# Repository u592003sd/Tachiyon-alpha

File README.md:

# Tachiyon-α MCU Developement Board

## Overview
- A minimalist Development Board design for a MSPM0C110x & MSPM0L130x MCUs.
- Low cost ARM Cortex M0+ MCU support

## Features
- Supports USB & SWD connection
- Powers up from Host USB port.

## Software Resources
- To be updated post PCB bring up.

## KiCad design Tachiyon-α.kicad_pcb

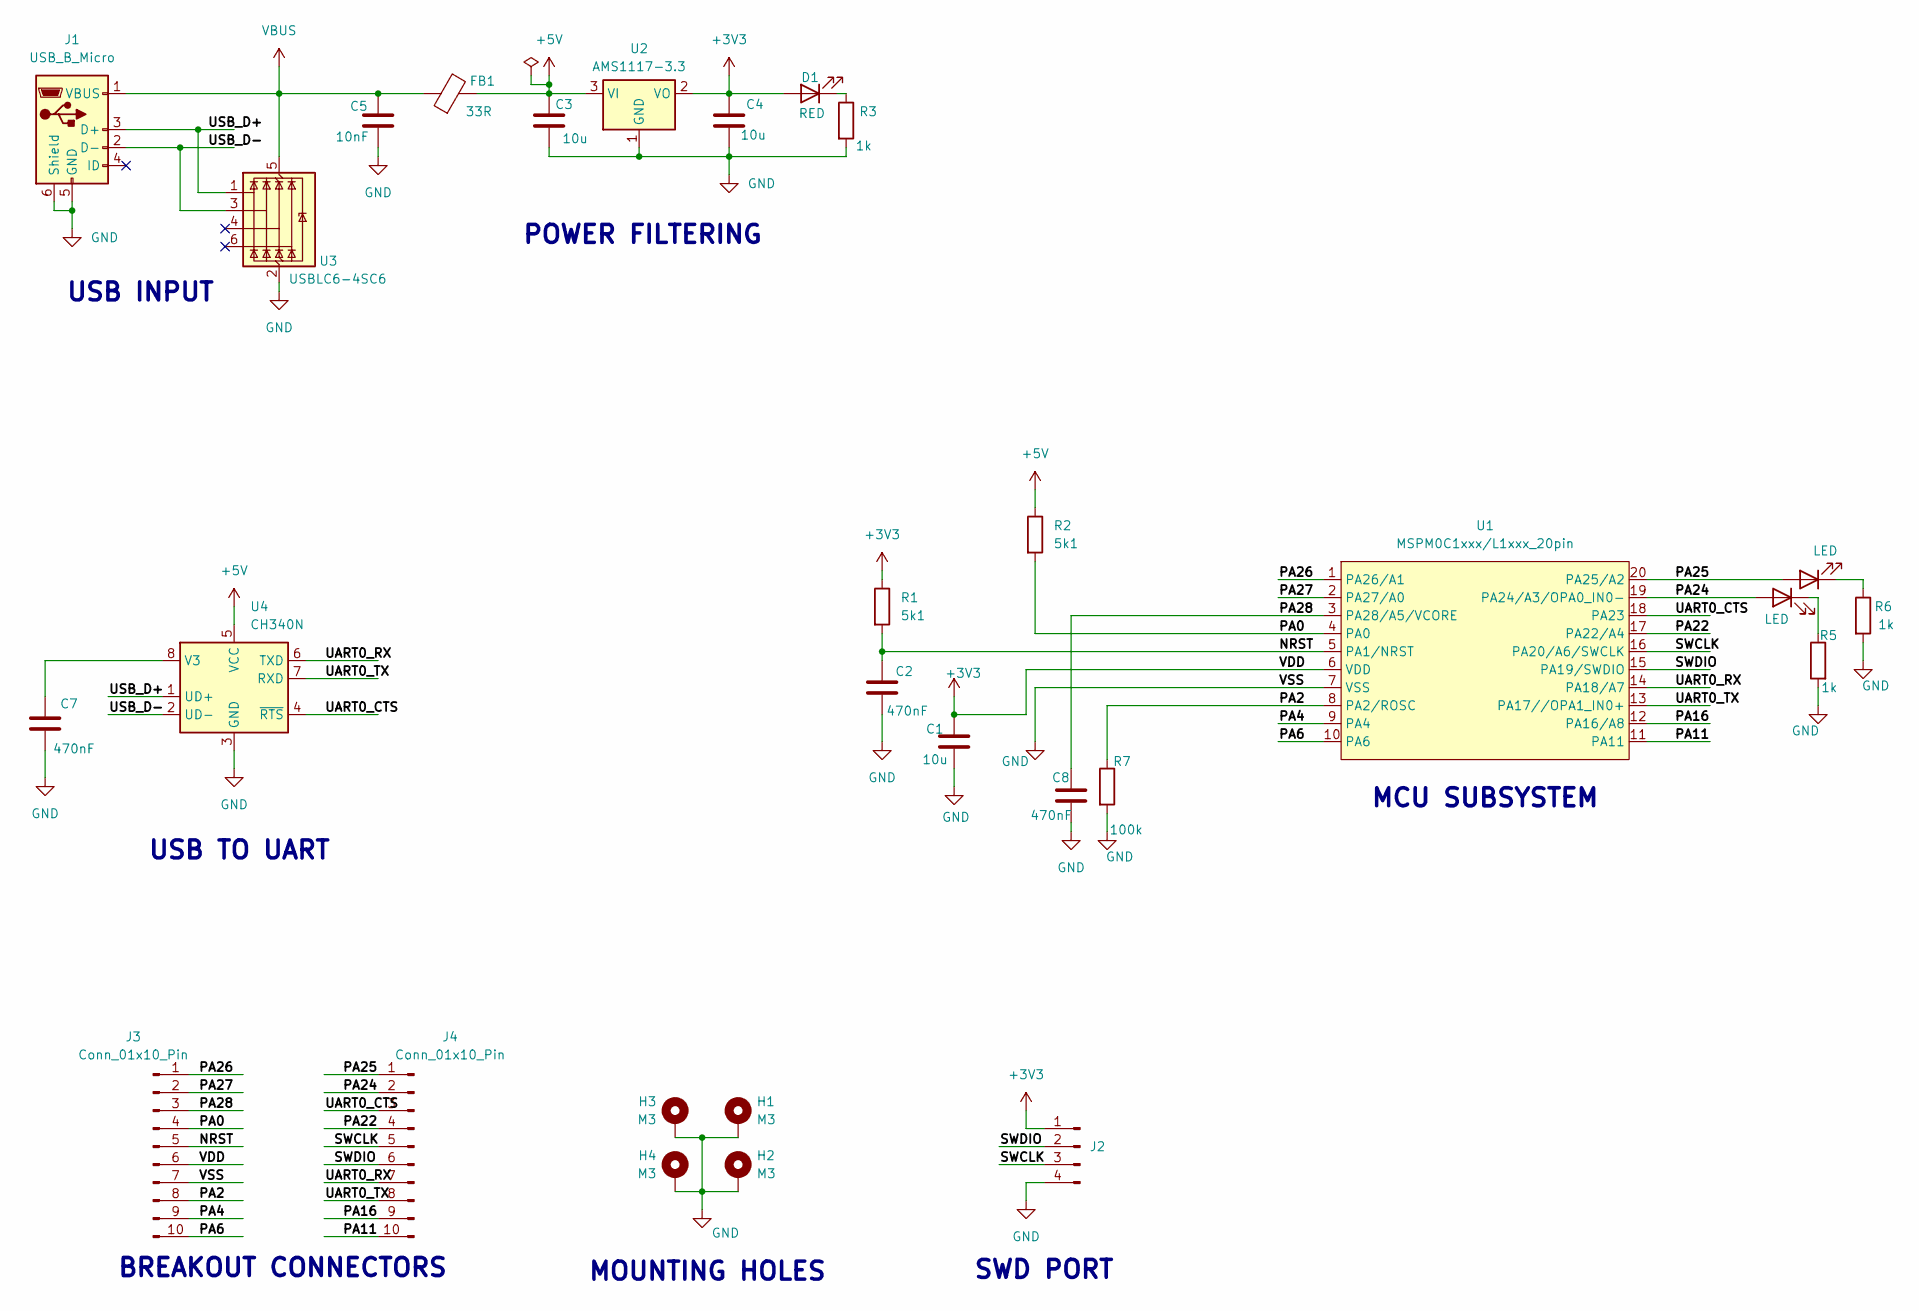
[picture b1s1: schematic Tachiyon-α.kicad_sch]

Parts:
C1, C3, C4: 10u; C_0603_1608Metric
C2, C7, C8: 470nF; C_0603_1608Metric
C5: 10nF; C_0603_1608Metric
D1: RED; D_1206_3216Metric
D2, D3: LED; D_1206_3216Metric
FB1: 33R; R_0603_1608Metric
H1, H2, H3, H4: M3; MountingHole_3.2mm_M3_Pad_Via
J1: USB_B_Micro; USB_Micro-B_Wuerth_629105150521
J2: Conn_01x04_Pin; PinHeader_1x04_P2.54mm_Horizontal
J3, J4: Conn_01x10_Pin; PinHeader_1x10_P2.54mm_Vertical
R1, R2: 5k1; R_0603_1608Metric
R3, R5, R6: 1k; R_0603_1608Metric
R7: 100k; R_0603_1608Metric
U1: MSPM0C1xxx/L1xxx_20pin; MSPM0C110xxDGS20_VSSOP-20_5.1x4.9mm_P0.5mm
U2: AMS1117-3.3; SOT-223-3_TabPin2
U3: USBLC6-4SC6; SOT-23-6
U4: CH340N; SOP-8_3.76x4.96mm_P1.27mm

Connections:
+3V3: C1.1, C4.1, D1.2 (A), J2.1, J3.6, R1.1, U1.6 (VDD), U2.2 (VO)
+5V: C3.1, FB1.2, R2.1, U2.3 (VI), U4.5 (VCC)
/NRST: C2.1, J3.5, R1.2, U1.5 (PA1/NRST)
/PA0: J3.4, R2.2, U1.4 (PA0)
/PA2: J3.8, R7.1, U1.8 (PA2/ROSC)
/PA4: J3.9, U1.9 (PA4)
/PA6: J3.10, U1.10 (PA6)
/PA11: J4.10, U1.11 (PA11)
/PA16: J4.9, U1.12 (PA16/A8)
/PA22: J4.4, U1.17 (PA22/A4)
/PA24: D2.2 (A), J4.2, U1.19 (PA24/A3/OPA0_IN0-)
/PA25: D3.2 (A), J4.1, U1.20 (PA25/A2)
/PA26: J3.1, U1.1 (PA26/A1)
/PA27: J3.2, U1.2 (PA27/A0)
/PA28: C8.1, J3.3, U1.3 (PA28/A5/VCORE)
/SWCLK: J2.3, J4.5, U1.16 (PA20/A6/SWCLK)
/SWDIO: J2.2, J4.6, U1.15 (PA19/SWDIO)
/UART0_CTS: J4.3, U1.18 (PA23), U4.4 (~RTS)
/UART0_RX: J4.7, U1.14 (PA18/A7), U4.6 (TXD)
/UART0_TX: J4.8, U1.13 (PA17//OPA1_IN0+), U4.7 (RXD)
/USB_D+: J1.3 (D+), U3.1 (I/O1), U4.1 (UD+)
/USB_D-: J1.2 (D-), U3.3 (I/O2), U4.2 (UD-)
GND: C1.2, C2.2, C3.2, C4.2, C5.2, C7.2, C8.2, H1.1, H2.1, H3.1, H4.1, J1.5 (GND), J1.6 (Shield), J2.4, J3.7, R3.2, R5.2, R6.2, R7.2, U1.7 (VSS), U2.1 (GND), U3.2 (GND), U4.3 (GND)
unnamed: D1.1 (K), R3.1
unnamed: D2.1 (K), R5.1
unnamed: D3.1 (K), R6.1
unnamed: C7.1, U4.8 (V3)
VBUS: C5.1, FB1.1, J1.1 (VBUS), U3.5 (VBUS)

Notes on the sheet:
MCU SUBSYSTEM
SWD PORT
POWER FILTERING
USB TO UART
BREAKOUT CONNECTORS
MOUNTING HOLES
USB INPUT

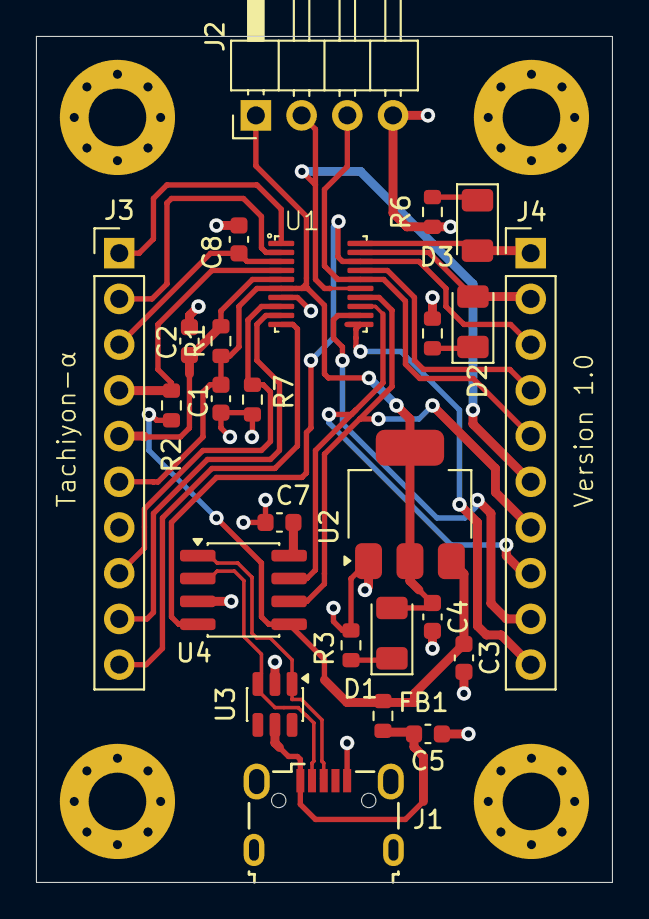
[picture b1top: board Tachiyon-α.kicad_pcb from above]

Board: 2 copper layers, 32.0 x 47.0 mm, 29 parts (0 on the bottom side), 28 nets.
